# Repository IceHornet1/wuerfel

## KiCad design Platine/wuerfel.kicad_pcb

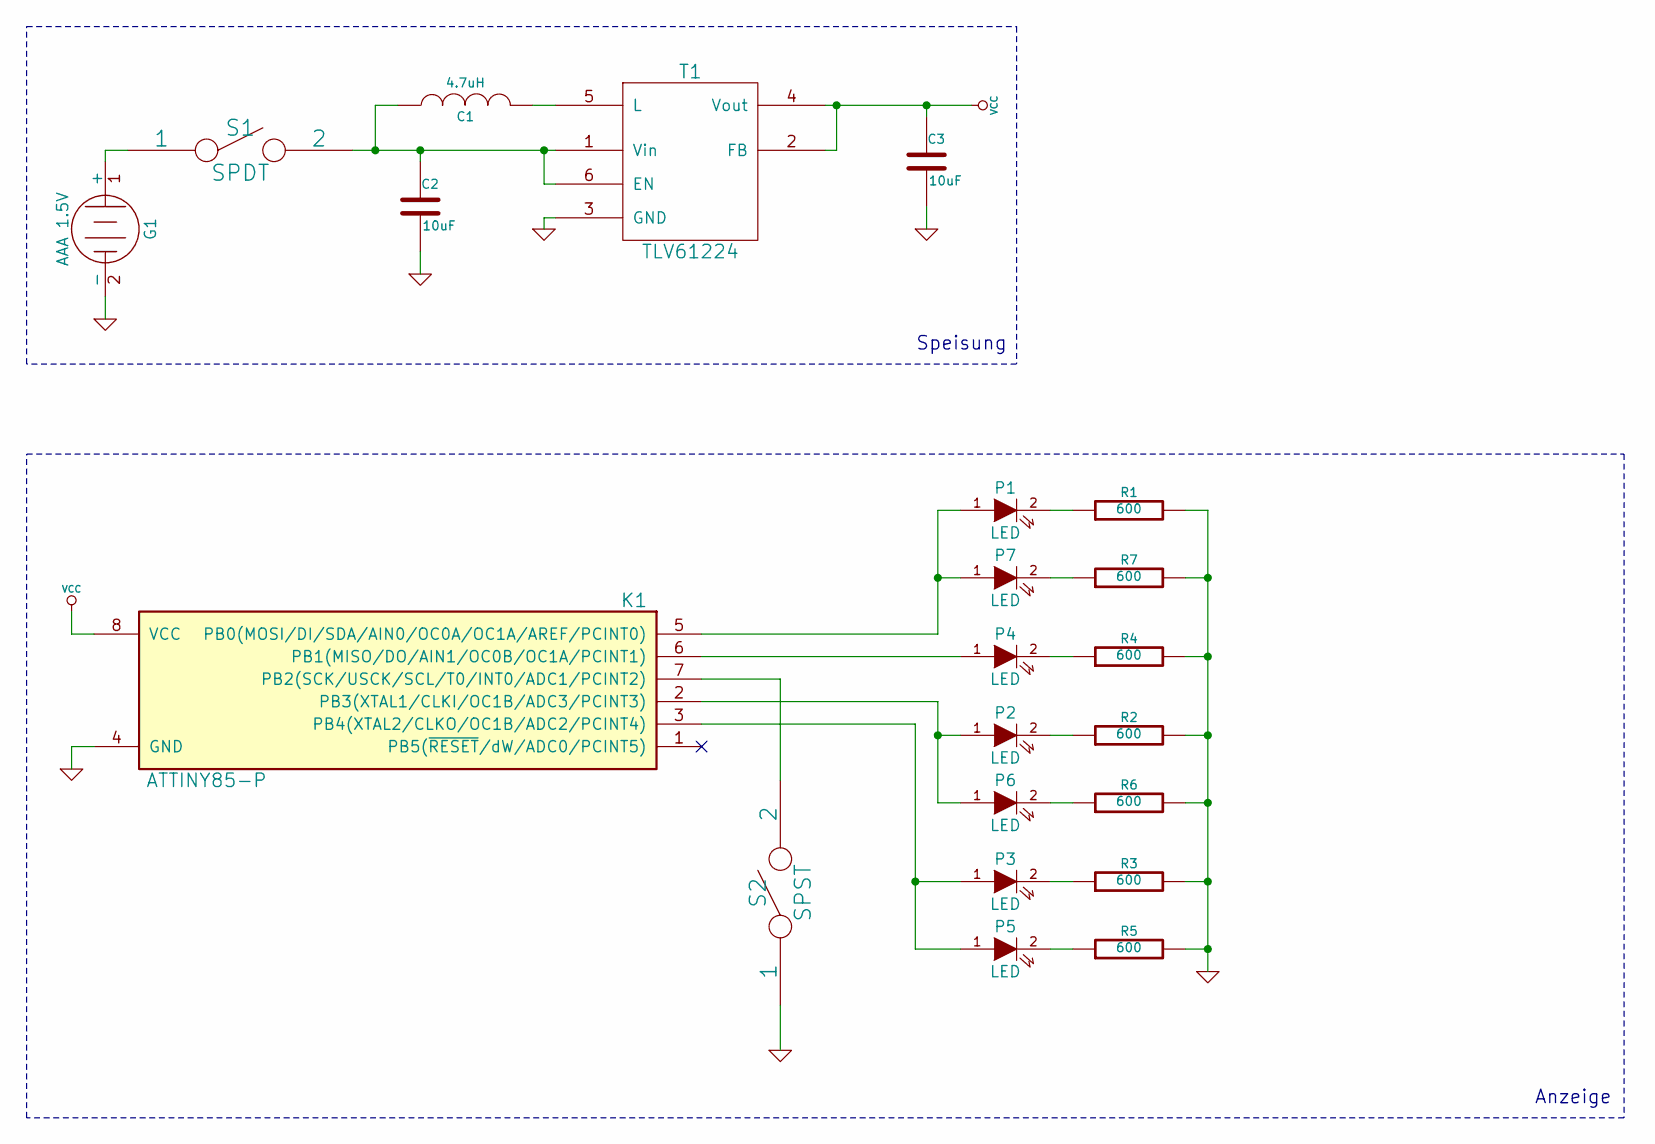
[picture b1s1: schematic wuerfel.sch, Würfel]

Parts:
C1: 4.7uH
C2, C3: 10uF
G1: AAA 1.5V
K1: ATTINY85-P; DIP8
P1, P2, P3, P4, P5, P6, P7: LED
R1, R2, R3, R4, R5, R6, R7: 600
S1: SPDT
S2: SPST
T1: TLV61224

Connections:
GND: C2.2, C3.2, G1.2 (-), K1.4 (GND), R1.2, R2.2, R3.2, R4.2, R5.2, R6.2, R7.2, S2.1, T1.3 (GND)
unnamed: K1.2 (PB3(XTAL1/CLKI/OC1B/ADC3/PCINT3)), P2.1 (A), P6.1 (A)
unnamed: K1.3 (PB4(XTAL2/CLKO/OC1B/ADC2/PCINT4)), P3.1 (A), P5.1 (A)
unnamed: K1.6 (PB1(MISO/DO/AIN1/OC0B/OC1A/PCINT1)), P4.1 (A)
unnamed: K1.5 (PB0(MOSI/DI/SDA/AIN0/OC0A/OC1A/AREF/PCI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), P1.1 (A), P7.1 (A)
unnamed: P7.2 (K), R7.1
unnamed: K1.7 (PB2(SCK/USCK/SCL/T0/INT0/ADC1/PCINT2)), S2.2
unnamed: P3.2 (K), R3.1
unnamed: P2.2 (K), R2.1
unnamed: P4.2 (K), R4.1
unnamed: P5.2 (K), R5.1
unnamed: P6.2 (K), R6.1
unnamed: P1.2 (K), R1.1
unnamed: C1.2, T1.5 (L)
unnamed: C1.1, C2.1, S1.2, T1.1 (Vin), T1.6 (EN)
unnamed: G1.1 (+), S1.1
VCC: C3.1, K1.8 (VCC), T1.2 (FB), T1.4 (Vout)

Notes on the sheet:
Speisung
Anzeige

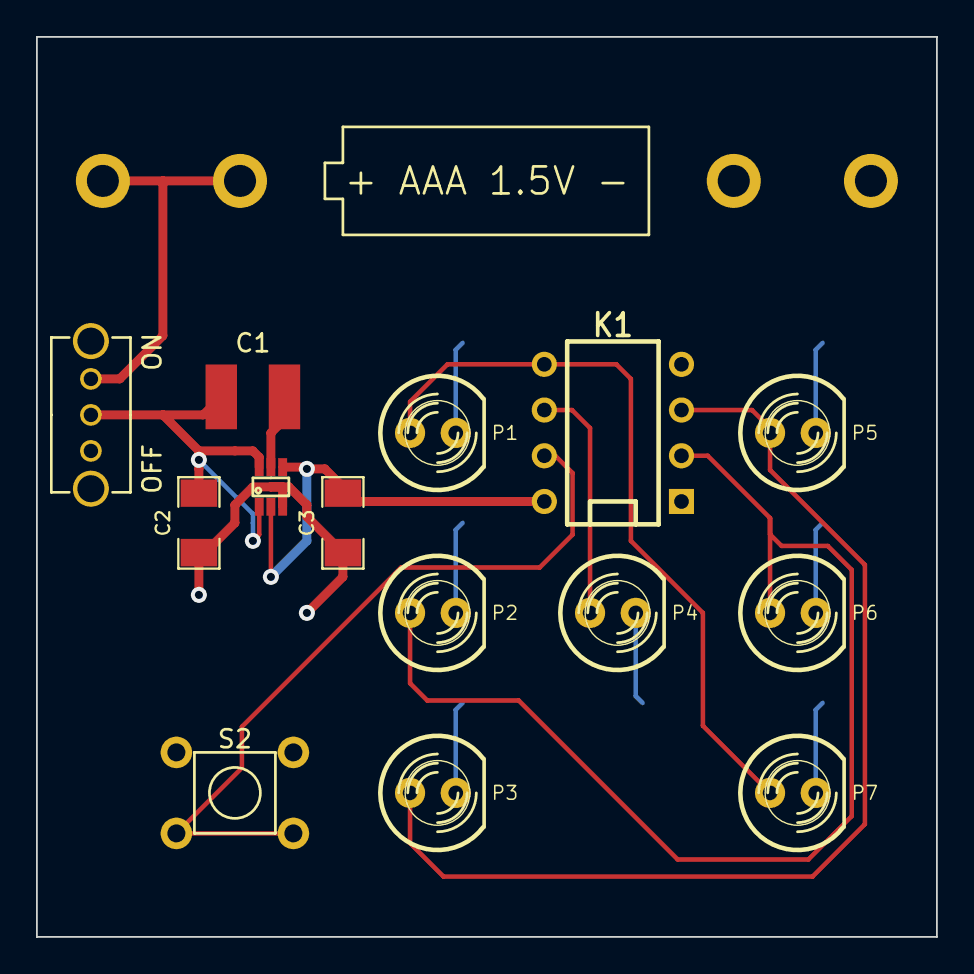
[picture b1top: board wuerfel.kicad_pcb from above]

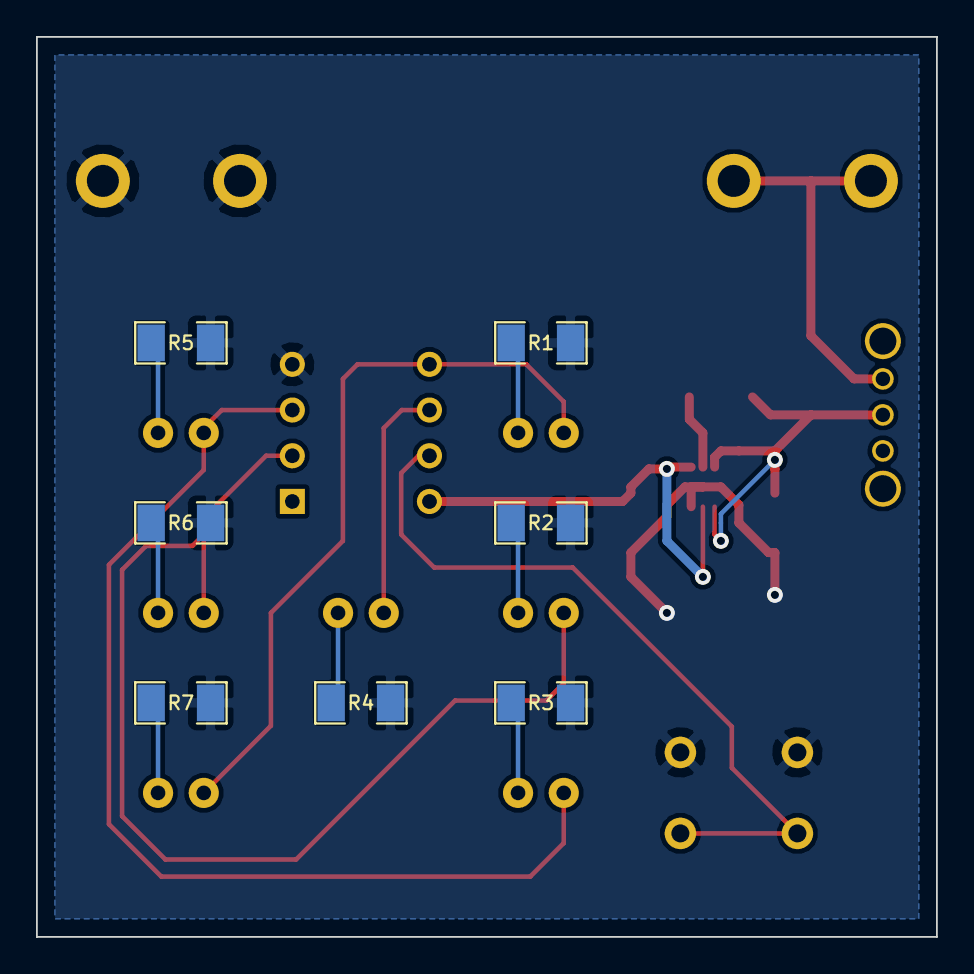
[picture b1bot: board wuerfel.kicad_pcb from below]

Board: 2 copper layers, 50.0 x 50.0 mm, 22 parts (7 on the bottom side), 17 nets.

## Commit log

2014-12-10 :octocat: Added .gitattributes
2014-12-10 Added initial file
2014-12-10 Added Startup
2014-12-10 Added seed, changed zahl to randNum
2014-12-10 Changed delay time
2014-12-10 changed startup times
2014-12-10 Different numbers each time
2014-12-10 commented out serial
2014-12-10 added entropy library
2014-12-11 Changed ints to bytes
2014-12-11 added display function
2014-12-16 Cleaned up the code
2014-12-16 Added sleep mode
2014-12-16 small changes to sleep
2014-12-16 changed stuff, doesn't work properly
2014-12-16 Release 1.0
2017-07-09 Added HW-Files
